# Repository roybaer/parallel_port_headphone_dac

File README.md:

# Parallel Port Headphone DAC

This is a reasonably accurate replica of the early 1990s SoundJr device by SiliconSoft,
a port-powered parallel port DAC that can directly drive 32 ohm headphones.

A comprehensive list of the SoundJr's features can be found on [the manufacturer's website](http://siliconsoft.com/sndjr1.htm).
The drivers for the SoundJr can be found in the [VOGONS Vintage Driver Library](http://www.vogonsdrivers.com/).

## Pictures

## Audio output

The primitive R-2R DAC will continuously convert the 8-bit PCM sample on the parallel port's data lines.
A PC program can therefore play PCM data by periodically writing PCM samples to the parallel port's data port.

## Volume control

The device's output volume can be set to one of nominally eight levels via the control port bits of the PC's parallel port.
Note that some of these signals are active-low.
There is also an implicit energy saving mode that is active whenever no port pin provides power to the device.

Ctrl 3..0 | Volume level
:---------|:------------
0000      | undefined (weaker 8)
0001      | undefined (weaker 6)
0010      | undefined (weaker 7)
0011      | undefined (weaker 5)
0100      | 8
0101      | 6
0110      | 7
0111      | 5
1000      | undefined (weaker 4)
1001      | undefined (weaker 2)
1010      | undefined (weaker 3)
1011      | muted, if data 1..0 = 0
1100      | 4
1101      | 2
1110      | 3
1111      | 1

## Component Substitution

Since the availability and pricing of components can vary widely over the course of decades, some component substitution can become necessary.
The following substitutions have been tested successfully:

Original component              | Acceptable substitute           | Type of component
:-------------------------------|:--------------------------------|:------------------
DAN202K (ROHM Semiconductor)    | M1MA152WKT1G (ON Semiconductor) | Double diode
767163203G (CTS Corporation)    | 4816P-1-203LF (Bourns Inc.)     | Resistor pack
767163103G (CTS Corporation)    | 4816P-1-103LF (Bourns Inc.)     | Resistor pack
MMST2222A (ROHM Semiconductor)  | MSD601-RT1G (ON Semiconductor)  | NPN transistor
MMST2907A (ROHM Semiconductor)  | MSA1162GT1G (ON Semiconductor)  | PNP transistor

The value of the two filter capacitors is unknown, but 1nF capacitors appear to work well enough.

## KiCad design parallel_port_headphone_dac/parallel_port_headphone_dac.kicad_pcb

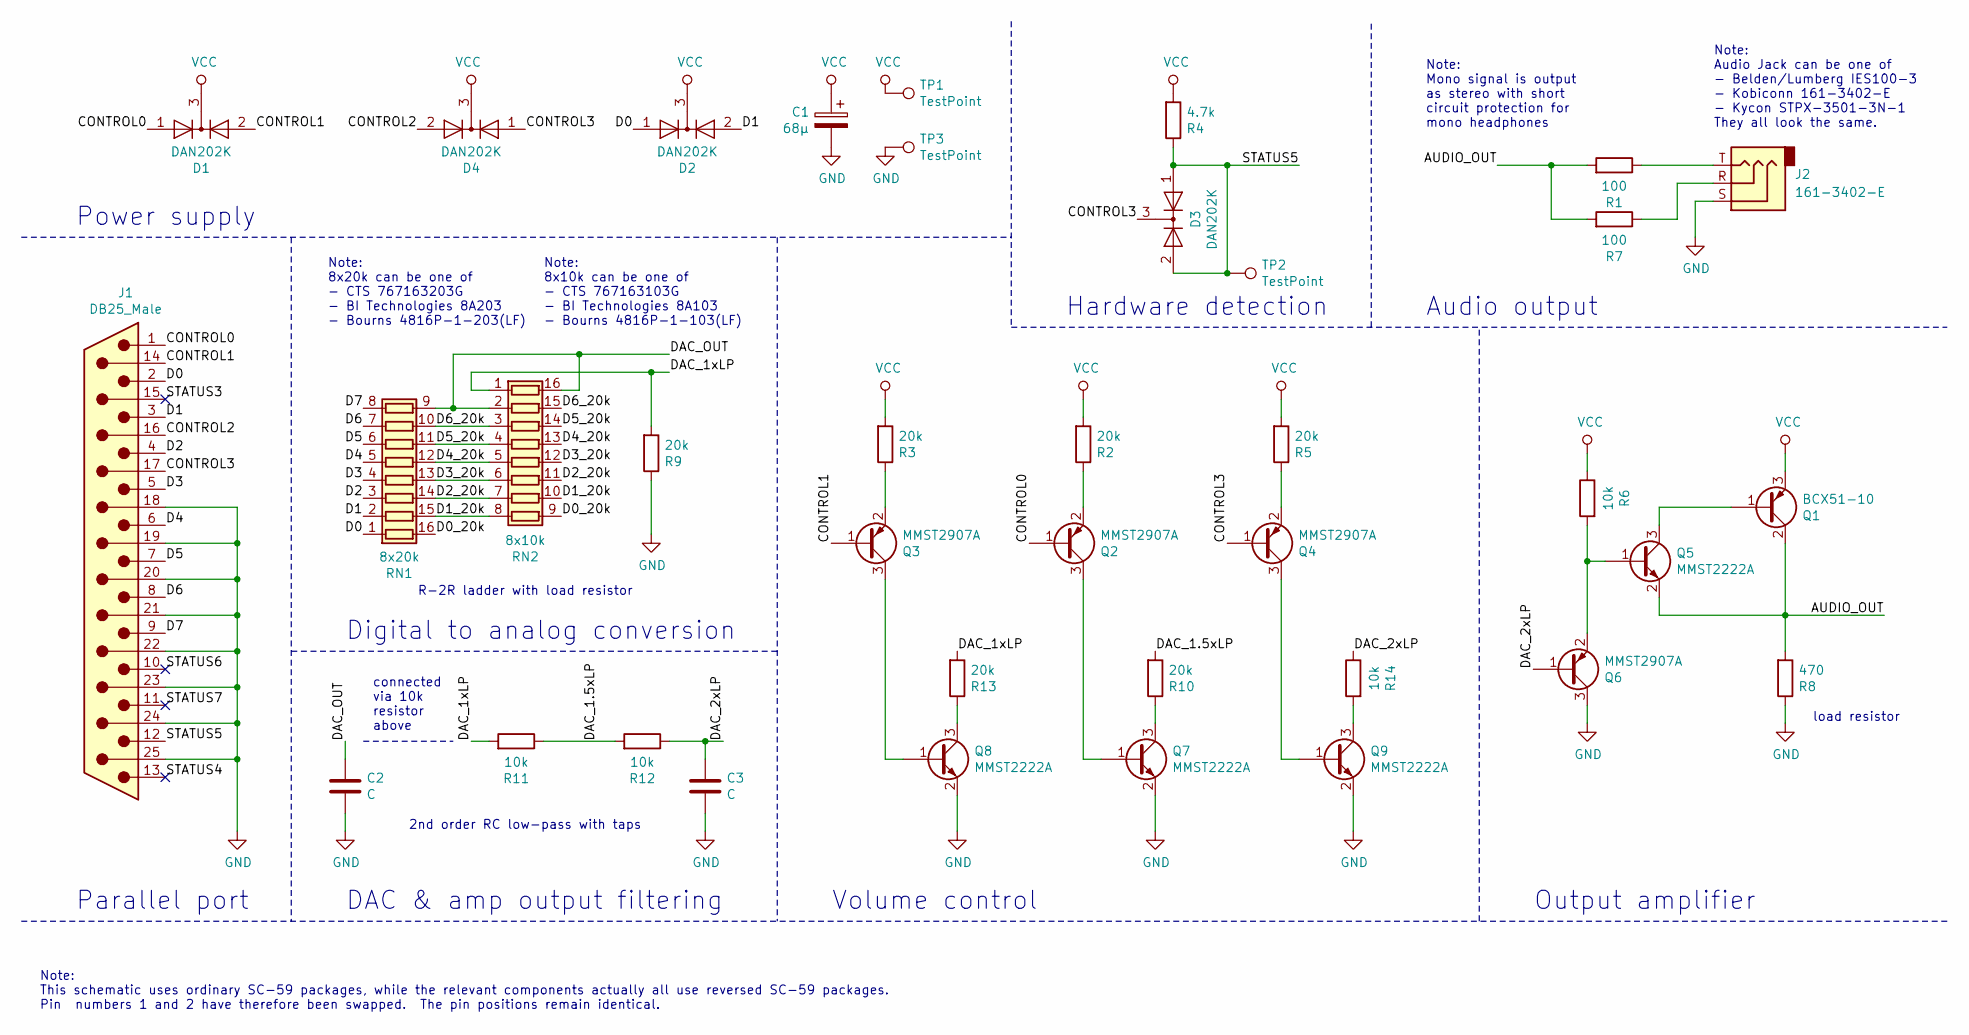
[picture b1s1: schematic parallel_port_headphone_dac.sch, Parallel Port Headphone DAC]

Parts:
C1: 68µ; CP_EIA-7343-30_AVX-N
C2, C3: C; C_0805_2012Metric
D1, D2, D3, D4: DAN202K; SC-59
J1: DB25_Male; DSUB-25_Male_EdgeMount_P2.77mm
J2: 161-3402-E; SoundJr_AudioJack
Q1: BCX51-10; SOT-89-3
Q2, Q3, Q4, Q6: MMST2907A; SC-59
Q5, Q7, Q8, Q9: MMST2222A; SC-59
R1, R7: 100; R_0805_2012Metric
R2, R3, R5, R9, R10, R13: 20k; R_0805_2012Metric
R4: 4.7k; R_0805_2012Metric
R6, R11, R12, R14: 10k; R_0805_2012Metric
R8: 470; R_0805_2012Metric
RN1: 8x20k; SOIC-16W_5.3x10.2mm_P1.27mm
RN2: 8x10k; SOIC-16W_5.3x10.2mm_P1.27mm
TP1, TP2, TP3: TestPoint; SolderWirePad_1x01_Drill0.8mm

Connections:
/AUDIO_OUT: Q1.2 (C), Q5.2 (E), R1.2, R7.2, R8.2
/CONTROL0: D1.1 (A), J1.1, Q2.1 (B)
/CONTROL1: D1.2 (A), J1.14, Q3.1 (B)
/CONTROL2: D4.2 (A), J1.16
/CONTROL3: D3.3 (K), D4.1 (A), J1.17, Q4.1 (B)
/D0: D2.1 (A), J1.2, RN1.1 (R1.1)
/D0_20k: RN1.16 (R1.2), RN2.9 (R8.2)
/D1: D2.2 (A), J1.3, RN1.2 (R2.1)
/D1_20k: RN1.15 (R2.2), RN2.8 (R8.1), RN2.10 (R7.2)
/D2: J1.4, RN1.3 (R3.1)
/D2_20k: RN1.14 (R3.2), RN2.7 (R7.1), RN2.11 (R6.2)
/D3: J1.5, RN1.4 (R4.1)
/D3_20k: RN1.13 (R4.2), RN2.6 (R6.1), RN2.12 (R5.2)
/D4: J1.6, RN1.5 (R5.1)
/D4_20k: RN1.12 (R5.2), RN2.5 (R5.1), RN2.13 (R4.2)
/D5: J1.7, RN1.6 (R6.1)
/D5_20k: RN1.11 (R6.2), RN2.4 (R4.1), RN2.14 (R3.2)
/D6: J1.8, RN1.7 (R7.1)
/D6_20k: RN1.10 (R7.2), RN2.3 (R3.1), RN2.15 (R2.2)
/D7: J1.9, RN1.8 (R8.1)
/DAC_1.5xLP: R10.2, R11.1, R12.2
/DAC_1xLP: R9.2, R11.2, R13.2, RN2.1 (R1.1)
/DAC_2xLP: C3.1, Q6.1 (B), R12.1, R14.1
/DAC_OUT: C2.1, RN1.9 (R8.2), RN2.2 (R2.1), RN2.16 (R1.2)
/STATUS3: J1.15
/STATUS4: J1.13
/STATUS5: D3.1 (A), D3.2 (A), J1.12, R4.1, TP2.1
/STATUS6: J1.10
/STATUS7: J1.11
GND: C1.2, C2.2, C3.2, J1.18, J1.19, J1.20, J1.21, J1.22, J1.23, J1.24, J1.25, J2.S, Q6.3 (C), Q7.2 (E), Q8.2 (E), Q9.2 (E), R8.1, R9.1, TP3.1
unnamed: J2.R, R7.1
unnamed: J2.T, R1.1
unnamed: Q1.1 (B), Q5.3 (C)
unnamed: Q2.2 (E), R2.1
unnamed: Q2.3 (C), Q7.1 (B)
unnamed: Q3.2 (E), R3.1
unnamed: Q3.3 (C), Q8.1 (B)
unnamed: Q4.2 (E), R5.1
unnamed: Q4.3 (C), Q9.1 (B)
unnamed: Q5.1 (B), Q6.2 (E), R6.2
unnamed: Q7.3 (C), R10.1
unnamed: Q8.3 (C), R13.1
unnamed: Q9.3 (C), R14.2
VCC: C1.1, D1.3 (K), D2.3 (K), D4.3 (K), Q1.3 (E), R2.2, R3.2, R4.2, R5.2, R6.1, TP1.1

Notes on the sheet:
Note: This schematic uses ordinary SC-59 packages, while the relevant components actually all use reversed SC-59 packages. Pin numbers 1 and 2 have therefore been swapped. The pin positions remain identical.
Note: Audio Jack can be one of - Belden/Lumberg IES100-3 - Kobiconn 161-3402-E - Kycon STPX-3501-3N-1 They all look the same.
Power supply
Hardware detection
Parallel port
Note: Mono signal is output as stereo with short circuit protection for mono headphones
Note: 8x20k can be one of - CTS 767163203G - BI Technologies 8A203 - Bourns 4816P-1-203(LF)
Note: 8x10k can be one of - CTS 767163103G - BI Technologies 8A103 - Bourns 4816P-1-103(LF)
2nd order RC low-pass with taps
Volume control
DAC & amp output filtering
Audio output
Output amplifier
load resistor
R-2R ladder with load resistor
Digital to analog conversion
connected via 10k resistor above

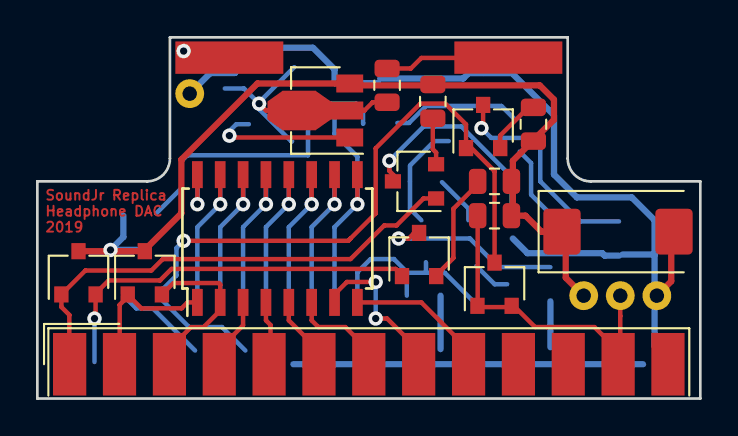
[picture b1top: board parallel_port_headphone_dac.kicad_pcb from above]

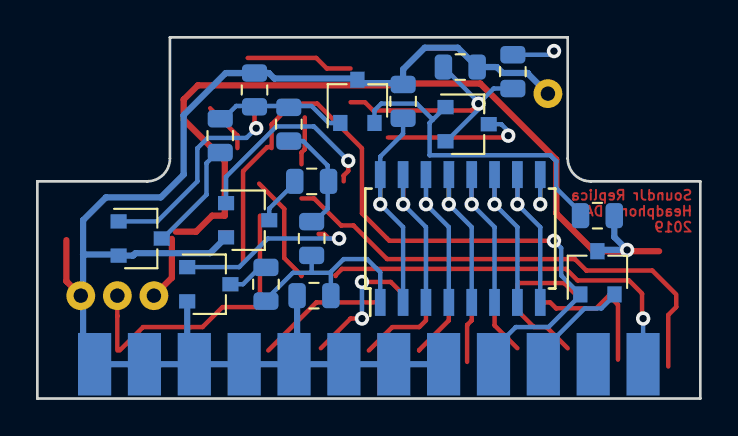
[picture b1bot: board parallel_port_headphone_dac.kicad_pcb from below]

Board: 2 copper layers, 36.8 x 20.1 mm, 37 parts (18 on the bottom side), 40 nets.

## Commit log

2019-07-20 add KiCAD files and PDF schematics
2019-07-20 add README.md
2021-08-29 improve documentation, add pictures
